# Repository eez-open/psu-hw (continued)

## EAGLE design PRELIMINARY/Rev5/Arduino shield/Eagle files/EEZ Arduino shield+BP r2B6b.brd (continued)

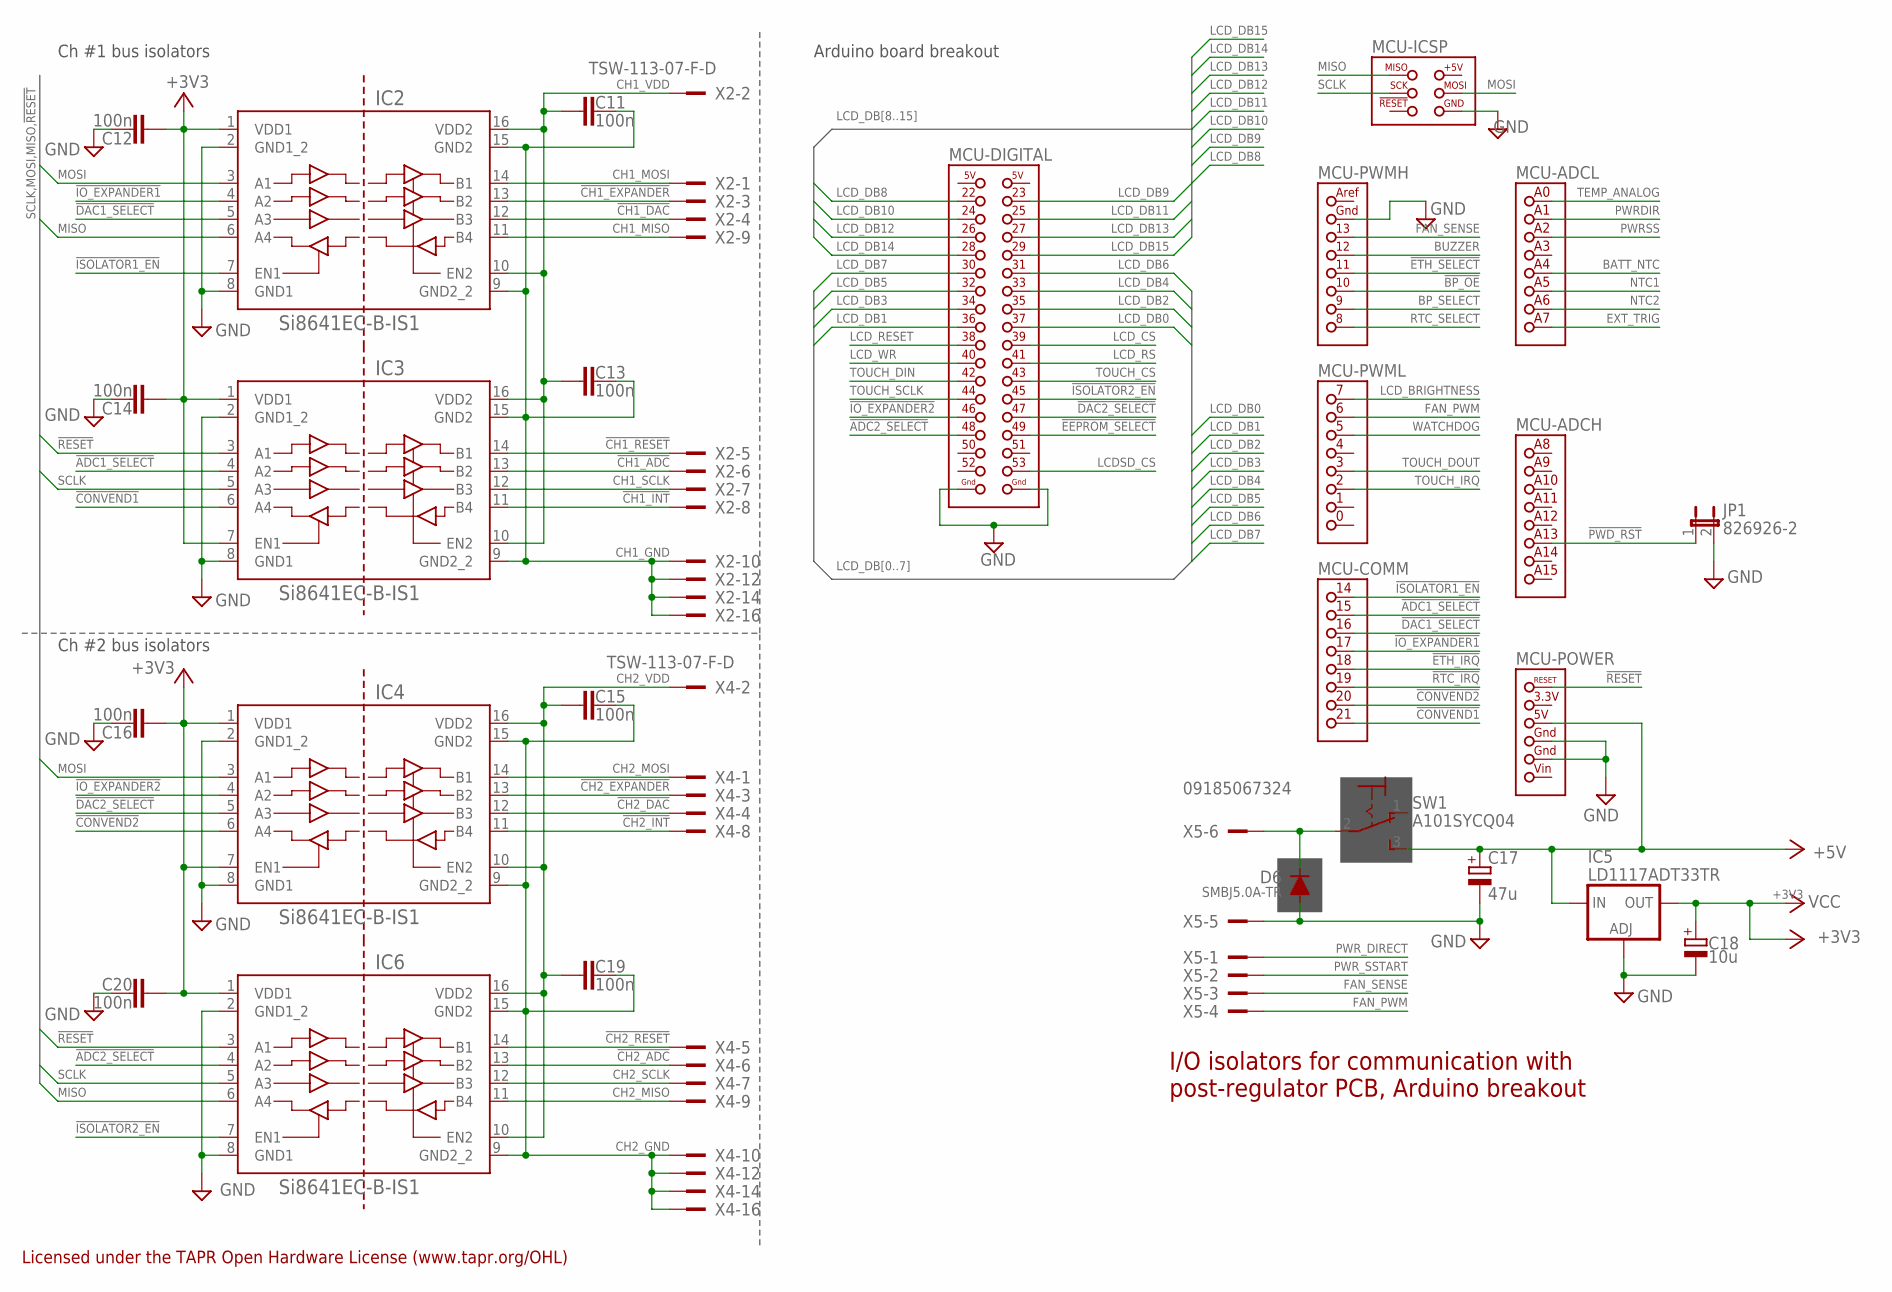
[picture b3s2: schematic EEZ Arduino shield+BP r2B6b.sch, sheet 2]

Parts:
C11, C12, C13, C14, C15, C16, C19, C20: 100n; C0603
C17: 47u; PANASONIC_C
C18: 10u; PANASONIC_C
D6: SMBJ5.0A-TR; DO214AA
IC2, IC3, IC4, IC6: Si8641EC-B-IS1; SOIC-16
IC5: LD1117ADT33TR; DPACK
JP1: 826926-2; JP1
MCU: Arduino Due; ARDUINO+ICSP_MIRROR
SW1: A101SYCQ04; M9040P
X2, X4: TSW-113-07-F-D; FARNELL 2025182
X5: 09185067324; IDC-6PIN

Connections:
!ADC1_SELECT: IC3.4 (A2), MCU.15
!ADC2_SELECT: IC6.4 (A2), MCU.48 (48(PL3))
!BP_OE: MCU.10; also elsewhere on the board
!CH1_ADC: IC3.13 (B2), X2.6
!CH1_DAC: IC2.12 (B3), X2.4
!CH1_EXPANDER: IC2.13 (B2), X2.3
!CH1_INT: IC3.11 (B4), X2.8
!CH1_RESET: IC3.14 (B1), X2.5
!CH2_ADC: IC6.13 (B2), X4.6
!CH2_DAC: IC4.12 (B3), X4.4
!CH2_EXPANDER: IC4.13 (B2), X4.3
!CH2_INT: IC4.11 (B4), X4.8
!CH2_RESET: IC6.14 (B1), X4.5
!CONVEND1: IC3.6 (A4), MCU.21
!CONVEND2: IC4.6 (A4), MCU.20
!DAC1_SELECT: IC2.5 (A3), MCU.16
!DAC2_SELECT: IC4.5 (A3), MCU.47 (47(PL4))
!EEPROM_SELECT: MCU.49 (49(PL2)); also elsewhere on the board
!ETH_IRQ: MCU.18; also elsewhere on the board
!ETH_SELECT: MCU.11; also elsewhere on the board
!IO_EXPANDER1: IC2.4 (A2), MCU.17
!IO_EXPANDER2: IC4.4 (A2), MCU.46 (46(PL5))
!ISOLATOR1_EN: IC2.7 (EN1), MCU.14
!ISOLATOR2_EN: IC6.7 (EN1), MCU.45 (45(PL6))
!PWD_RST: JP1.1, MCU.A13 (ADC13)
!RESET: IC3.3 (A1), IC6.3 (A1), MCU.RESET (!RESET); also elsewhere on the board
!RTC_IRQ: MCU.19; also elsewhere on the board
+3V3: C12.1, C14.1, C16.1, C18.1 (+), C20.1, IC2.1 (VDD1), IC3.1 (VDD1), IC3.7 (EN1), IC4.1 (VDD1), IC4.7 (EN1), IC5.4 (OUT), IC6.1 (VDD1); also elsewhere on the board
+5V: C17.1 (+), IC5.3 (IN), MCU.5V, SW1.3 (S); also elsewhere on the board
BATT_NTC: MCU.A4 (ADC4); also elsewhere on the board
BP_SELECT: MCU.9 (9(PH6)); also elsewhere on the board
BUZZER: MCU.12; also elsewhere on the board
CH1_GND: C11.2, C13.2, IC2.9 (GND2_2), IC2.15 (GND2), IC3.9 (GND2_2), IC3.15 (GND2), X2.10, X2.12, X2.14, X2.16; also elsewhere on the board
CH1_MISO: IC2.11 (B4), X2.9
CH1_MOSI: IC2.14 (B1), X2.1
CH1_SCLK: IC3.12 (B3), X2.7
CH1_VDD: C11.1, C13.1, IC2.10 (EN2), IC2.16 (VDD2), IC3.10 (EN2), IC3.16 (VDD2), X2.2; also elsewhere on the board
CH2_GND: C15.2, C19.2, IC4.9 (GND2_2), IC4.15 (GND2), IC6.9 (GND2_2), IC6.15 (GND2), X4.10, X4.12, X4.14, X4.16; also elsewhere on the board
CH2_MISO: IC6.11 (B4), X4.9
CH2_MOSI: IC4.14 (B1), X4.1
CH2_SCLK: IC6.12 (B3), X4.7
CH2_VDD: C15.1, C19.1, IC4.10 (EN2), IC4.16 (VDD2), IC6.10 (EN2), IC6.16 (VDD2), X4.2
EXT_TRIG: MCU.A7 (ADC7); also elsewhere on the board
FAN_PWM: MCU.6 (6(PH3)), X5.4
FAN_SENSE: MCU.13, X5.3
GND: C12.2, C14.2, C16.2, C17.2 (-), C18.2 (-), C20.2, D6.A, IC2.2 (GND1_2), IC2.8 (GND1), IC3.2 (GND1_2), IC3.8 (GND1), IC4.2 (GND1_2), IC4.8 (GND1), IC5.1 (ADJ), IC6.2 (GND1_2), IC6.8 (GND1), JP1.2, MCU.GND, MCU.GND1, MCU.GND2, MCU.GND3, MCU.GND4, MCU.ICSP_GND (GND), X5.5; also elsewhere on the board
LCDSD_CS: MCU.53 (53(PB2/MOSI)); also elsewhere on the board
LCD_BRIGHTNESS: MCU.7 (7(PH4)); also elsewhere on the board
LCD_CS: MCU.39 (39(PC0)); also elsewhere on the board
LCD_DB0: MCU.37 (37(PC2)); also elsewhere on the board
LCD_DB1: MCU.36 (36(PC3)); also elsewhere on the board
LCD_DB2: MCU.35 (35(PC4)); also elsewhere on the board
LCD_DB3: MCU.34 (34(PC5)); also elsewhere on the board
LCD_DB4: MCU.33 (33(PC6)); also elsewhere on the board
LCD_DB5: MCU.32 (32(PC7)); also elsewhere on the board
LCD_DB6: MCU.31 (31(PA7)); also elsewhere on the board
LCD_DB7: MCU.30 (30(PA6)); also elsewhere on the board
LCD_DB8: MCU.22; also elsewhere on the board
LCD_DB9: MCU.23; also elsewhere on the board
LCD_DB10: MCU.24 (24(PA0)); also elsewhere on the board
LCD_DB11: MCU.25 (25(PA1)); also elsewhere on the board
LCD_DB12: MCU.26 (26(PA2)); also elsewhere on the board
LCD_DB13: MCU.27 (27(PA3)); also elsewhere on the board
LCD_DB14: MCU.28 (28(PA4)); also elsewhere on the board
LCD_DB15: MCU.29 (29(PA5)); also elsewhere on the board
LCD_RESET: MCU.38 (38(PC1)); also elsewhere on the board
LCD_RS: MCU.41 (41(PG2)); also elsewhere on the board
LCD_WR: MCU.40 (40(PD7)); also elsewhere on the board
MISO: IC2.6 (A4), IC6.6 (A4), MCU.ICSP_MISO (MISO); also elsewhere on the board
MOSI: IC2.3 (A1), IC4.3 (A1), MCU.ICSP_MOSI (MOSI); also elsewhere on the board
unnamed: D6.C, SW1.2, X5.6
NTC1: MCU.A5 (ADC5); also elsewhere on the board
NTC2: MCU.A6 (ADC6); also elsewhere on the board
PWRDIR: MCU.A1 (ADC1); also elsewhere on the board
PWRSS: MCU.A2 (ADC2); also elsewhere on the board
PWR_DIRECT: X5.1; also elsewhere on the board
PWR_SSTART: X5.2; also elsewhere on the board
RTC_SELECT: MCU.8 (8(PH5)); also elsewhere on the board
SCLK: IC3.5 (A3), IC6.5 (A3), MCU.ICSP_SCK (SCK); also elsewhere on the board
TEMP_ANALOG: MCU.A0 (ADC0); also elsewhere on the board
TOUCH_CS: MCU.43 (43(PG0)); also elsewhere on the board
TOUCH_DIN: MCU.42 (42(PG1)); also elsewhere on the board
TOUCH_DOUT: MCU.3 (3(PE5)); also elsewhere on the board
TOUCH_IRQ: MCU.2 (2(PE4)); also elsewhere on the board
TOUCH_SCLK: MCU.44 (44(PL7)); also elsewhere on the board
WATCHDOG: MCU.5 (5(PE3)); also elsewhere on the board

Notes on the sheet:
I/O isolators for communication with
post-regulator PCB, Arduino breakout
Ch #1 bus isolators
Ch #2 bus isolators
Arduino board breakout
Licensed under the TAPR Open Hardware License (www.tapr.org/OHL)

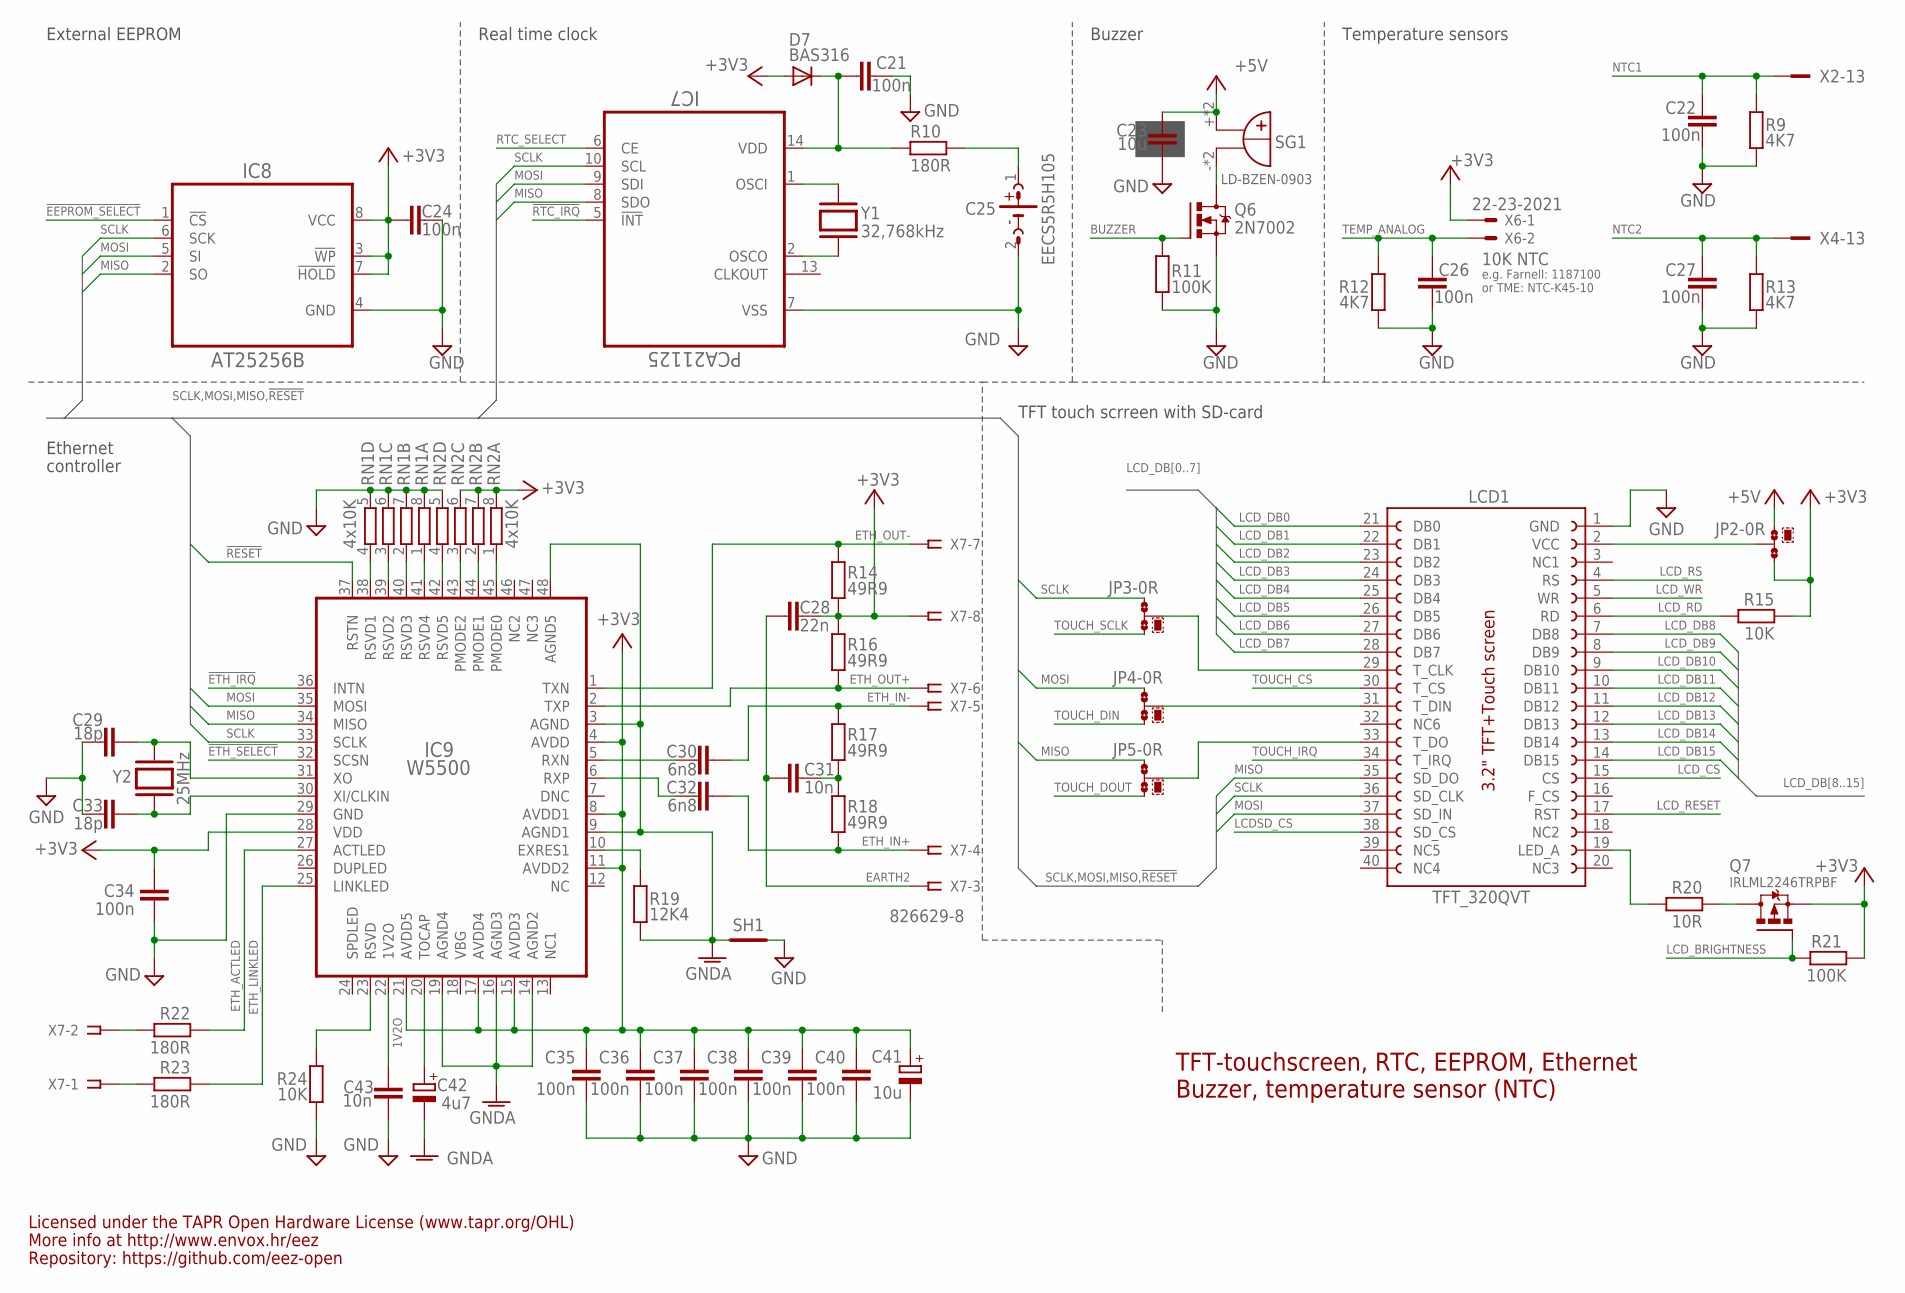
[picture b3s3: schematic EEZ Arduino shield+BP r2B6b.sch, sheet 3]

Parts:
C21, C22, C24, C26, C27, C34, C35, C36, C37, C38, C39, C40: 100n; C0603
C23: 10u; C1206
C25: EECS5R5H105; SG-R20MM
C28: 22n; C0805
C29, C33: 18p; C0603
C30, C32: 6n8; C0603
C31, C43: 10n; C0805
C41: 10u; EC1206
C42: 4u7; EC1206
D7: BAS316; SOD323-W
IC7: PCA21125; SOP65P640X120-14N
IC8: AT25256B; SOIC127P600X175-8N
IC9: W5500; TQFP48-7X7
JP2, JP3, JP4, JP5: 0R-JUMPA; A0R-JMP
LCD1: TFT_320QVT; LCD_TFT_320QVT_MIRROR
Q6: 2N7002; SOT103P240X110-3N
Q7: IRLML2246TRPBF; SOT95P237X112-3N
R9, R12, R13: 4K7; R0805
R10, R22, R23: 180R; R0805
R11, R21: 100K; R0805
R14, R16, R17, R18: 49R9; R0805
R15, R24: 10K; R0805
R19: 12K4; R0805
R20: 10R; R0805
RN1, RN2: 4x10K; CAY16
SG1: LD-BZEN-0903; BUZZER
SH1: SHORTNOHOLE; SHORT_NOHOLE
X2, X4: TSW-113-07-F-D; FARNELL 2025182
X6: 22-23-2021; MPN 22-23-2021
X7: 826629-8; SSW-108-02-S-S; MPN SSW-108-02-S-S
Y1: 32,768kHz; R26_XTAL
Y2: 25MHz; HC-49/4H

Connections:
1V2O: C43.2, IC9.22 (1V2O)
!EEPROM_SELECT: IC8.1 (!CS); also elsewhere on the board
!ETH_IRQ: IC9.36 (INTN); also elsewhere on the board
!ETH_SELECT: IC9.32 (SCSN); also elsewhere on the board
!RESET: IC9.37 (RSTN); also elsewhere on the board
!RTC_IRQ: IC7.5 (!INT); also elsewhere on the board
+3V3: C24.1, C28.1, C34.2, C35.1, C36.1, C37.1, C38.1, C39.1, C40.1, C41.+, D7.A, IC8.3 (!WP), IC8.7 (!HOLD), IC8.8 (VCC), IC9.4 (AVDD), IC9.8 (AVDD1), IC9.11 (AVDD2), IC9.15 (AVDD3), IC9.17 (AVDD4), IC9.21 (AVDD5), IC9.28 (VDD), JP2.3, Q7.2 (S), R14.1, R15.2, R16.2, R21.2, RN2.6 (2), RN2.7 (2), RN2.8 (2), X6.1, X7.8; also elsewhere on the board
+5V: C23.2, JP2.1, SG1.+, SG1.+B (+); also elsewhere on the board
BUZZER: Q6.1 (G), R11.2; also elsewhere on the board
EARTH2: C28.2, C31.2, X7.3; also elsewhere on the board
ETH_ACTLED: IC9.27 (ACTLED), R22.1
ETH_IN+: C32.1, R18.1, X7.4
ETH_IN-: C30.1, R17.2, X7.5
ETH_LINKLED: IC9.25 (LINKLED), R23.1
ETH_OUT+: IC9.2 (TXP), R16.1, X7.6
ETH_OUT-: IC9.1 (TXN), R14.2, X7.7
GND: C21.1, C22.1, C23.1, C24.2, C25.2 (-), C26.1, C27.1, C29.2, C33.2, C34.1, C35.2, C36.2, C37.2, C38.2, C39.2, C40.2, C41.-, C43.1, IC7.7 (VSS), IC8.4 (GND), IC9.29 (GND), LCD1.1 (GND), Q6.2 (S), R9.2, R11.1, R12.2, R13.2, R24.1, RN1.5 (2), RN1.6 (2), RN1.7 (2), RN1.8 (2), RN2.5 (2), SH1.P$1 (GND_A); also elsewhere on the board
GNDA: C42.-, IC9.3 (AGND), IC9.9 (AGND1), IC9.14 (AGND2), IC9.16 (AGND3), IC9.19 (AGND4), IC9.48 (AGND5), R19.1, SH1.P$2 (GND_B)
LCDSD_CS: LCD1.38 (SD_CS); also elsewhere on the board
LCD_BRIGHTNESS: Q7.1 (G), R21.1; also elsewhere on the board
LCD_CS: LCD1.15 (CS); also elsewhere on the board
LCD_DB0: LCD1.21 (DB0); also elsewhere on the board
LCD_DB1: LCD1.22 (DB1); also elsewhere on the board
LCD_DB2: LCD1.23 (DB2); also elsewhere on the board
LCD_DB3: LCD1.24 (DB3); also elsewhere on the board
LCD_DB4: LCD1.25 (DB4); also elsewhere on the board
LCD_DB5: LCD1.26 (DB5); also elsewhere on the board
LCD_DB6: LCD1.27 (DB6); also elsewhere on the board
LCD_DB7: LCD1.28 (DB7); also elsewhere on the board
LCD_DB8: LCD1.7 (DB8); also elsewhere on the board
LCD_DB9: LCD1.8 (DB9); also elsewhere on the board
LCD_DB10: LCD1.9 (DB10); also elsewhere on the board
LCD_DB11: LCD1.10 (DB11); also elsewhere on the board
LCD_DB12: LCD1.11 (DB12); also elsewhere on the board
LCD_DB13: LCD1.12 (DB13); also elsewhere on the board
LCD_DB14: LCD1.13 (DB14); also elsewhere on the board
LCD_DB15: LCD1.14 (DB15); also elsewhere on the board
LCD_RD: LCD1.6 (RD), R15.1
LCD_RESET: LCD1.17 (RST); also elsewhere on the board
LCD_RS: LCD1.4 (RS); also elsewhere on the board
LCD_WR: LCD1.5 (WR); also elsewhere on the board
LED_A: LCD1.19 (LED_A), R20.2
MISO: IC7.8 (SDO), IC8.2 (SO), IC9.34 (MISO), JP5.1, LCD1.35 (SD_DO); also elsewhere on the board
MOSI: IC7.9 (SDI), IC8.5 (SI), IC9.35 (MOSI), JP4.1, LCD1.37 (SD_IN); also elsewhere on the board
unnamed: JP5.2, LCD1.33 (T_DO)
unnamed: C33.1, IC9.30 (XI/CLKIN), Y2.2
unnamed: IC9.23 (RSVD), R24.2
unnamed: C30.2, IC9.5 (RXN)
unnamed: C32.2, IC9.6 (RXP)
unnamed: JP2.2, LCD1.2 (VCC)
unnamed: IC9.43 (PMODE2), RN2.3 (1)
unnamed: IC9.44 (PMODE1), RN2.2 (1)
unnamed: Q7.3 (D), R20.1
unnamed: IC9.45 (PMODE0), RN2.1
unnamed: IC9.42 (RSVD5), RN2.4 (1)
unnamed: JP4.2, LCD1.31 (T_DIN)
unnamed: JP3.2, LCD1.29 (T_CLK)
unnamed: C25.1 (+), R10.1
unnamed: IC9.38 (RSVD1), RN1.4 (1)
unnamed: IC7.1 (OSCI), Y1.1
unnamed: IC7.2 (OSCO), Y1.2
unnamed: IC9.39 (RSVD2), RN1.3 (1)
unnamed: IC9.41 (RSVD4), RN1.1
unnamed: IC9.40 (RSVD3), RN1.2 (1)
unnamed: R23.2, X7.1
unnamed: R22.2, X7.2
unnamed: IC9.10 (EXRES1), R19.2
unnamed: Q6.3 (D), SG1.-, SG1.-B (-)
unnamed: C29.1, IC9.31 (XO), Y2.1
unnamed: C21.2, D7.C, IC7.14 (VDD), R10.2
unnamed: C31.1, R17.1, R18.2
NTC1: C22.2, R9.1, X2.13; also elsewhere on the board
NTC2: C27.2, R13.1, X4.13; also elsewhere on the board
RTC_SELECT: IC7.6 (CE); also elsewhere on the board
SCLK: IC7.10 (SCL), IC8.6 (SCK), IC9.33 (SCLK), JP3.1, LCD1.36 (SD_CLK); also elsewhere on the board
TEMP_ANALOG: C26.2, R12.1, X6.2; also elsewhere on the board
TOCAP: C42.+, IC9.20 (TOCAP)
TOUCH_CS: LCD1.30 (T_CS); also elsewhere on the board
TOUCH_DIN: JP4.3; also elsewhere on the board
TOUCH_DOUT: JP5.3; also elsewhere on the board
TOUCH_IRQ: LCD1.34 (T_IRQ); also elsewhere on the board
TOUCH_SCLK: JP3.3; also elsewhere on the board

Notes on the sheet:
TFT-touchscreen, RTC, EEPROM, Ethernet
e.g. Farnell: 1187100
10K NTC
or TME: NTC-K45-10
Buzzer, temperature sensor (NTC)
External EEPROM
Real time clock
Buzzer
Temperature sensors
TFT touch scrreen with SD-card
Ethernet
controller
Licensed under the TAPR Open Hardware License (www.tapr.org/OHL)
Repository: https://github.com/eez-open
More info at http://www.envox.hr/eez

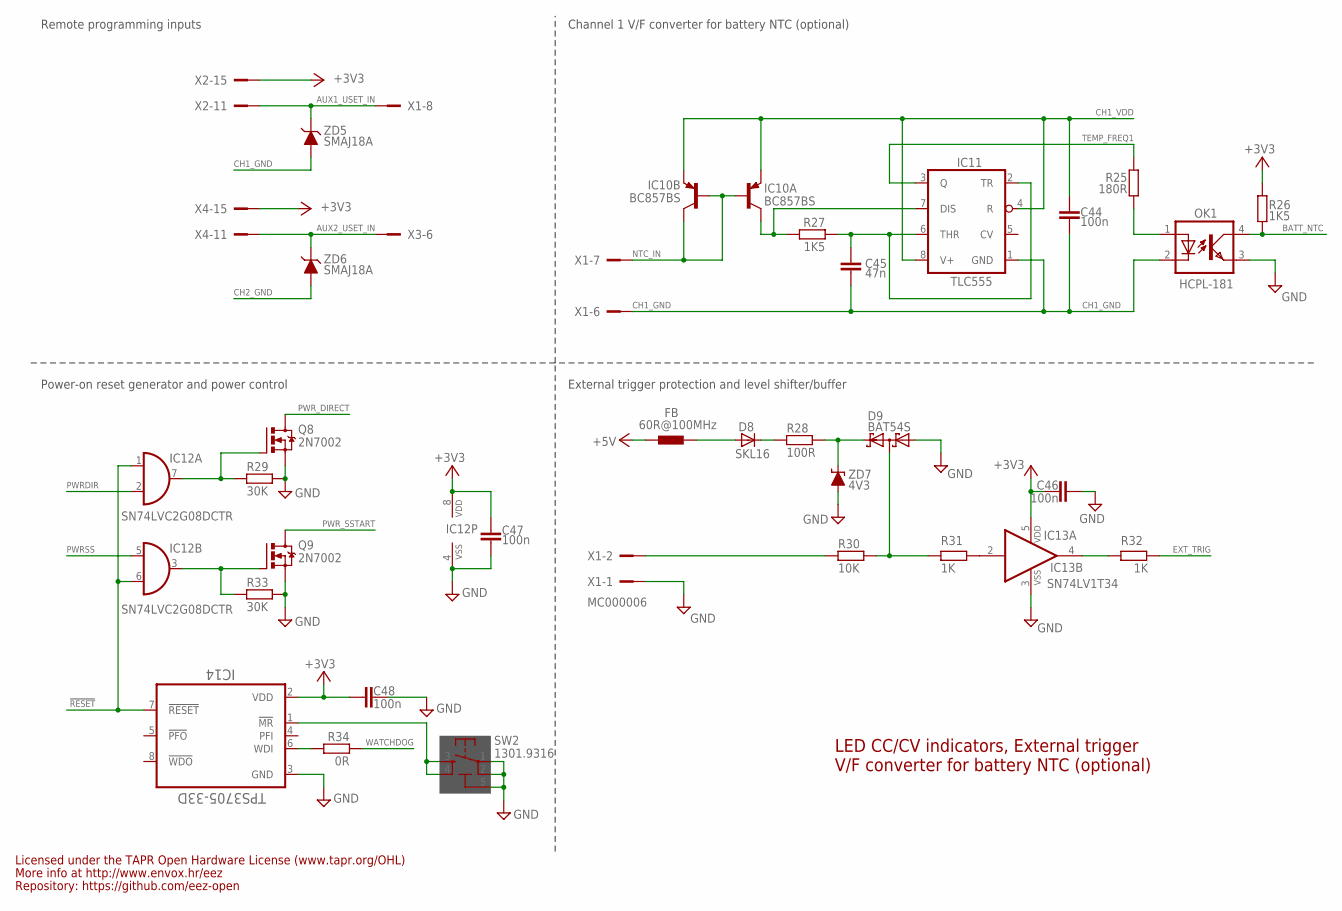
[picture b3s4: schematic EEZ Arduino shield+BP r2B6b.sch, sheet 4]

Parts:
C44, C46, C47, C48: 100n; C0603
C45: 47n; C0805
D8: SKL16; DO214AC
D9: BAT54S; SOT23
FB: 60R@100MHz; BEAD0603
IC10: BC857BS; SOT65P210X110-6N
IC11: TLC555; SOIC127P600X175-8N
IC12: SN74LVC2G08DCTR; SOP65P400X130-8N
IC13: SN74LV1T34; SOT95P280X145-5N
IC14: TPS3705-33D; SOIC127P600X175-8N
OK1: HCPL-181
Q8, Q9: 2N7002; SOT103P240X110-3N
R25: 180R; R0805
R26, R27: 1K5; R0805
R28: 100R; R0805
R29, R33: 30K; R0805
R30: 10K; R1206
R31, R32: 1K; R0805
R34: 0R; R0805
SW2: 1301.9316; TACTM-6XN
X1: MC000006; MC000006_MIRROR; FARNELL 2007972
X2, X4: TSW-113-07-F-D; FARNELL 2025182
X3: MC000005; MC000005_MIRROR
ZD5, ZD6: SMAJ18A; DO214AC
ZD7: 4V3; MINIMELF

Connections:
!RESET: IC12.1 (I0), IC12.6 (I1), IC14.7 (!RESET); also elsewhere on the board
+3V3: C46.1, C47.2, C48.2, IC12.8 (VDD), IC13.5 (VDD), IC14.2 (VDD), R26.1, X2.15, X4.15; also elsewhere on the board
+5V: FB.P$1 (1); also elsewhere on the board
AUX1_USET_IN: X1.8, X1.8.1, X2.11, ZD5.C
AUX2_USET_IN: X3.6, X3.6.1, X4.11, ZD6.C
BATT_NTC: OK1.4 (COL), R26.2; also elsewhere on the board
CH1_GND: C44.2, C45.1, IC11.1 (GND), OK1.2 (C), X1.6, X1.6.1, ZD5.A; also elsewhere on the board
CH1_VDD: C44.1, IC10.1 (E), IC10.4 (E), IC11.4 (R), IC11.8 (V+); also elsewhere on the board
CH2_GND: ZD6.A; also elsewhere on the board
EXT_TRIG: R32.1; also elsewhere on the board
GND: C46.2, C47.1, C48.1, D9.1 (A1), IC12.4 (VSS), IC13.3 (VSS), IC14.3 (GND), OK1.3 (EMIT), Q8.2 (S), Q9.2 (S), R29.2, R33.2, SW2.1, SW2.2, SW2.5 (5-GND), X1.1, X1.1.1, ZD7.A; also elsewhere on the board
unnamed: OK1.1 (A), R25.2
unnamed: IC10.6 (C), IC11.7 (DIS), R27.1
unnamed: C45.2, IC11.2 (TR), IC11.6 (THR), R27.2
unnamed: D9.2 (C2), R28.1, ZD7.C
unnamed: D9.3 (C1A2), R30.2, R31.2
unnamed: IC13.2 (I), R31.1
unnamed: IC13.4 (O), R32.2
unnamed: D8.C, R28.2
unnamed: R30.1, X1.2, X1.2.1
unnamed: D8.A, FB.P$2 (2)
unnamed: IC14.1 (!MR), SW2.3, SW2.4
unnamed: IC14.6 (WDI), R34.1
unnamed: IC12.7 (O), Q8.1 (G), R29.1
unnamed: IC12.3 (O), Q9.1 (G), R33.1
NTC_IN: IC10.2 (B), IC10.3 (C), IC10.5 (B), X1.7, X1.7.1
PWRDIR: IC12.2 (I1); also elsewhere on the board
PWRSS: IC12.5 (I0); also elsewhere on the board
PWR_DIRECT: Q8.3 (D); also elsewhere on the board
PWR_SSTART: Q9.3 (D); also elsewhere on the board
TEMP_FREQ1: IC11.3 (Q), R25.1
WATCHDOG: R34.2; also elsewhere on the board

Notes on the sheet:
V/F converter for battery NTC (optional)
LED CC/CV indicators, External trigger
Channel 1 V/F converter for battery NTC (optional)
External trigger protection and level shifter/buffer
Remote programming inputs
Licensed under the TAPR Open Hardware License (www.tapr.org/OHL)
Repository: https://github.com/eez-open
More info at http://www.envox.hr/eez
Power-on reset generator and power control

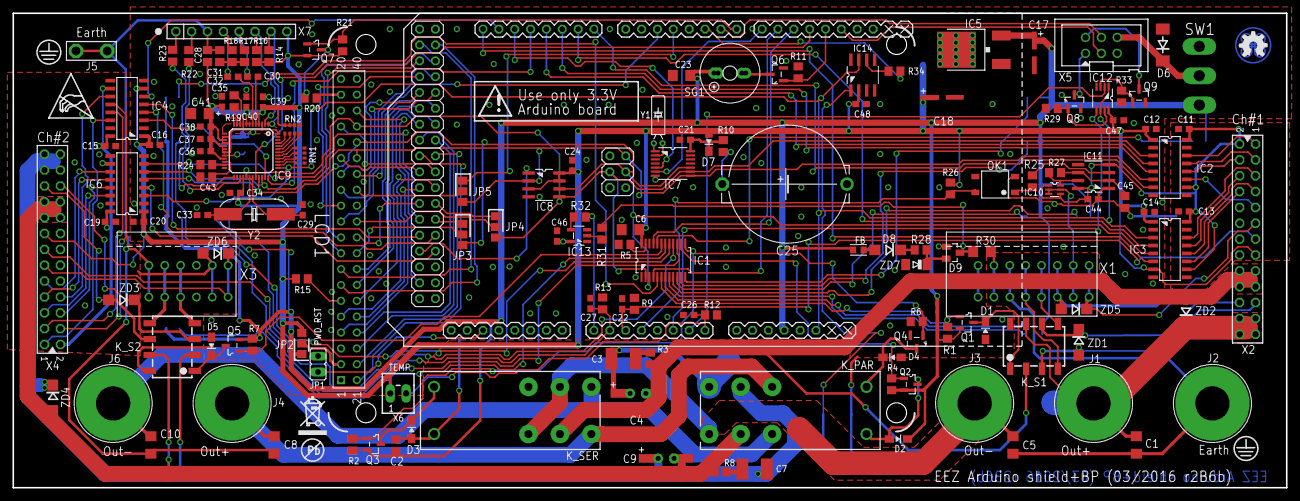
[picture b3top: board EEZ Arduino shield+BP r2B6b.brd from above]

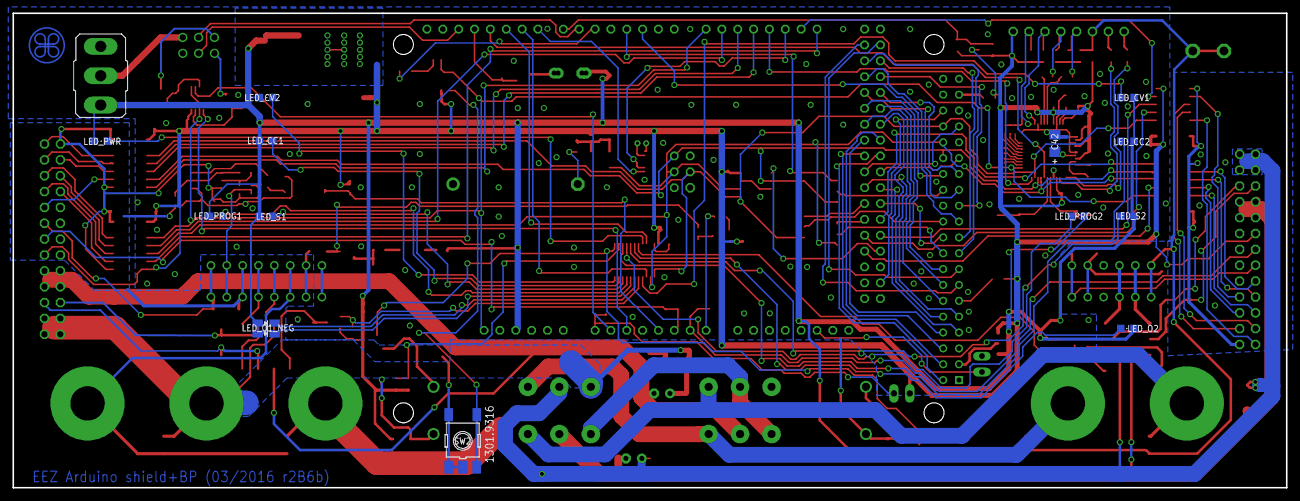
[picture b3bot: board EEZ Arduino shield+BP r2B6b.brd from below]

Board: 3 copper layers, 204.0 x 76.0 mm, 170 parts (14 on the bottom side), 183 nets.

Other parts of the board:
EEZ_SIGNATURE: SIGNATURESMALL; SIGNATURE_5MM
U$2: RECYCLE_BIN1/8
U$3: PB_SMALL
U$4: ESD_SYMBOL

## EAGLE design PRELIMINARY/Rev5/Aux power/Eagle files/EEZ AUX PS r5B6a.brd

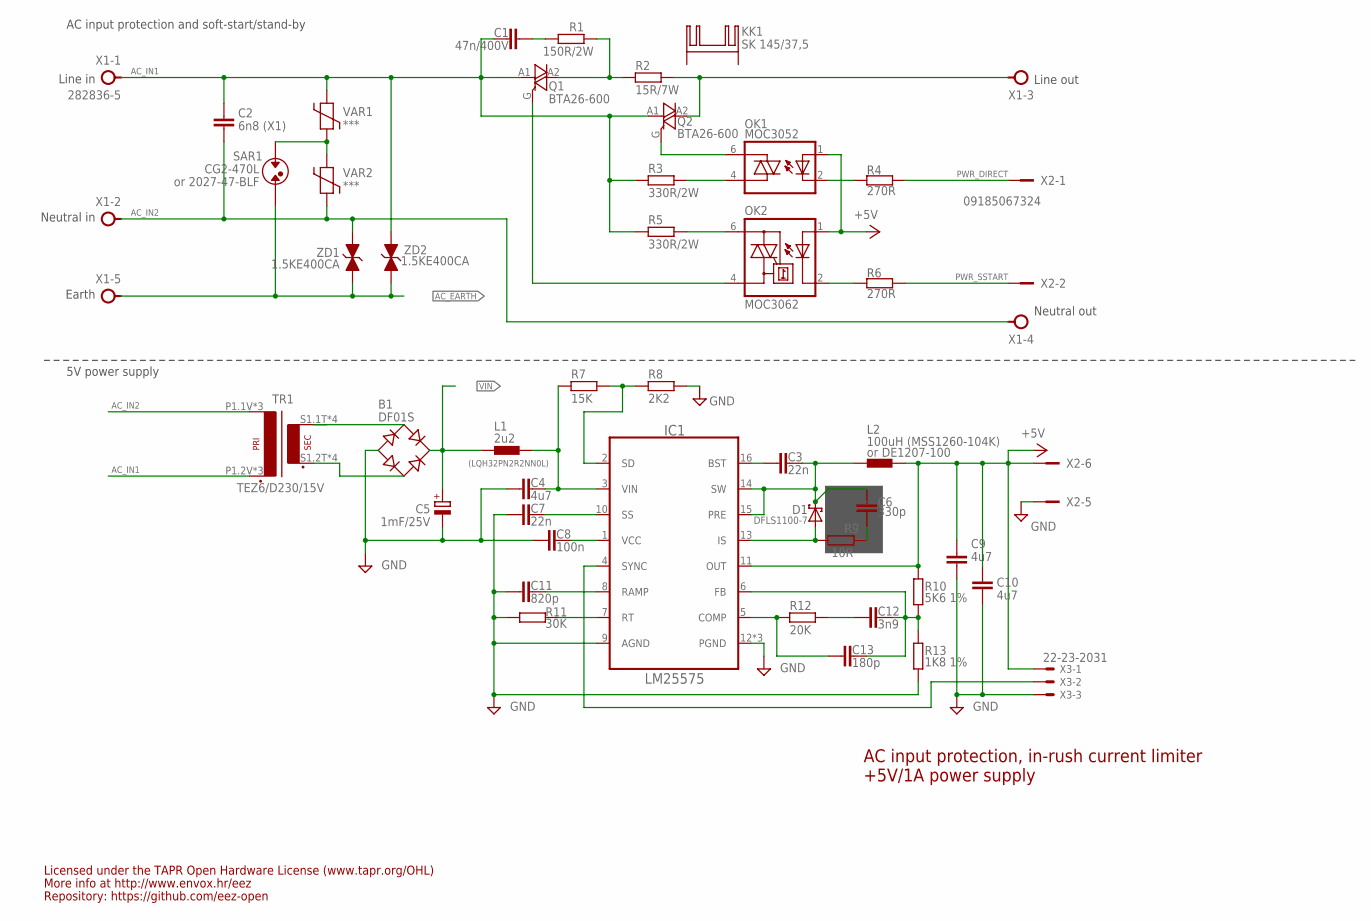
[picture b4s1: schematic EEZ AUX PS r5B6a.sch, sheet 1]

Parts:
B1: DF01S; DFS
C1: 47n/400V; C075-052X106
C2: 6n8 (X1); C102-064X133
C3, C7: 22n; C0805
C4, C9, C10: 4u7; C1210
C5: 1mF/25V; ECAP5/10.5
C6: 330p; C0805
C8: 100n; C0805
C11: 820p; C0805
C12: 3n9; C0805
C13: 180p; C0805
D1: DFLS1100-7; SOD123
IC1: LM25575; SOP65P640X110-17N_HOLE
KK1: SK 145/37,5; SK145
L1: 2u2; L1210
L2: 100uH (MSS1260-104K); MSS1278
OK1: MOC3052; DIL6-SMD
OK2: MOC3062; DIL6-SMD; MPN MOC3033S-M
Q1, Q2: BTA26-600; TOP3S-1
R1: 150R/2W; R2512
R2: 15R/7W; R_0913
R3, R5: 330R/2W; R2512
R4, R6: 270R; R0805
R7: 15K; R0805
R8: 2K2; R0805
R9: 10R; R1206
R10: 5K6 1%; R0805
R11: 30K; R0805
R12: 20K; R0805
R13: 1K8 1%; R0805
SAR1: CG2-470L; SAR
TR1: TEZ6/D230/15V; PCB_TRAFO6VA_TEZ+VPP
VAR1, VAR2: ***; VARISTOR
X1: 282836-5; TBLOCK5.0_5
X2: 09185067324; IDC-6PIN
X3: 22-23-2031
ZD1, ZD2: 1.5KE400CA; DO201-BIDIR

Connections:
+5V: C9.1, C10.1, IC1.11 (OUT), L2.2, OK1.1 (A), OK2.1 (A), R10.1, X2.6, X3.1; also elsewhere on the board
AC_EARTH: SAR1.P$2, X1.5, ZD1.C (1), ZD2.C (1); also elsewhere on the board
AC_IN1: C1.2, C2.1, Q1.A1, Q2.A1, R3.2, R5.2, TR1.P1.2V (P2), TR1.P2.2V (P2), TR1.P2_TEZ (P2), VAR1.P$2, X1.1, ZD2.A (2)
AC_IN2: C2.2, TR1.P1.1V (P1), TR1.P1_TEZ (P1), TR1.P2.1V (P1), VAR2.P$1, X1.2, X1.4, ZD1.A (2)
DC_PREG1: C4.1, IC1.3 (VIN), L1.2, R7.2
GND: B1.-, C4.2, C5.-, C7.2, C8.1, C9.2, C10.2, C11.1, IC1.9 (AGND), IC1.12 (PGND), IC1.TP (PGND), IC1.TP2 (PGND), R8.1, R11.2, R13.2, X2.5, X3.3; also elsewhere on the board
IS: D1.A, IC1.13 (IS), R9.1
unnamed: C6.2, R9.2
unnamed: OK1.6 (A2), Q2.G
unnamed: OK1.4 (A1), R3.1
unnamed: OK2.4 (A1), Q1.G
unnamed: OK1.2 (C), R4.1
unnamed: OK2.2 (C), R6.1
unnamed: OK2.6 (A2), R5.1
unnamed: Q2.A2, R2.2, X1.3
unnamed: B1.AC1, TR1.S1.1T (S1), TR1.S1.1V (S1), TR1.S2.1T (S1), TR1.S2.1V (S1)
unnamed: IC1.4 (SYNC), X3.2
unnamed: C1.1, R1.1
unnamed: B1.AC2, TR1.S1.2T (S2), TR1.S1.2V (S2), TR1.S2.2T (S2), TR1.S2.2V (S2)
unnamed: Q1.A2, R1.2, R2.1
unnamed: C12.2, R12.2
unnamed: SAR1.P$1, VAR1.P$1, VAR2.P$2
unnamed: C12.1, C13.1, IC1.6 (FB), R10.2, R13.1
unnamed: C3.2, IC1.16 (BST)
unnamed: C13.2, IC1.5 (COMP), R12.1
unnamed: IC1.7 (RT), R11.1
unnamed: C8.2, IC1.1 (VCC)
unnamed: C11.2, IC1.8 (RAMP)
unnamed: C7.1, IC1.10 (SS)
unnamed: IC1.2 (SD), R7.1, R8.2
PWR_DIRECT: R4.2, X2.1
PWR_SSTART: R6.2, X2.2
SW: C3.1, C6.1, D1.C, IC1.14 (SW), IC1.15 (PRE), L2.1
VIN: B1.+, C5.+, L1.1; also elsewhere on the board

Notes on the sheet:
AC input protection, in-rush current limiter
+5V/1A power supply
Line in
Neutral in
Earth
or DE1207-100
Line out
Neutral out
or 2027-47-BLF
(LQH32PN2R2NN0L)
Licensed under the TAPR Open Hardware License (www.tapr.org/OHL)
Repository: https://github.com/eez-open
More info at http://www.envox.hr/eez
5V power supply
AC input protection and soft-start/stand-by

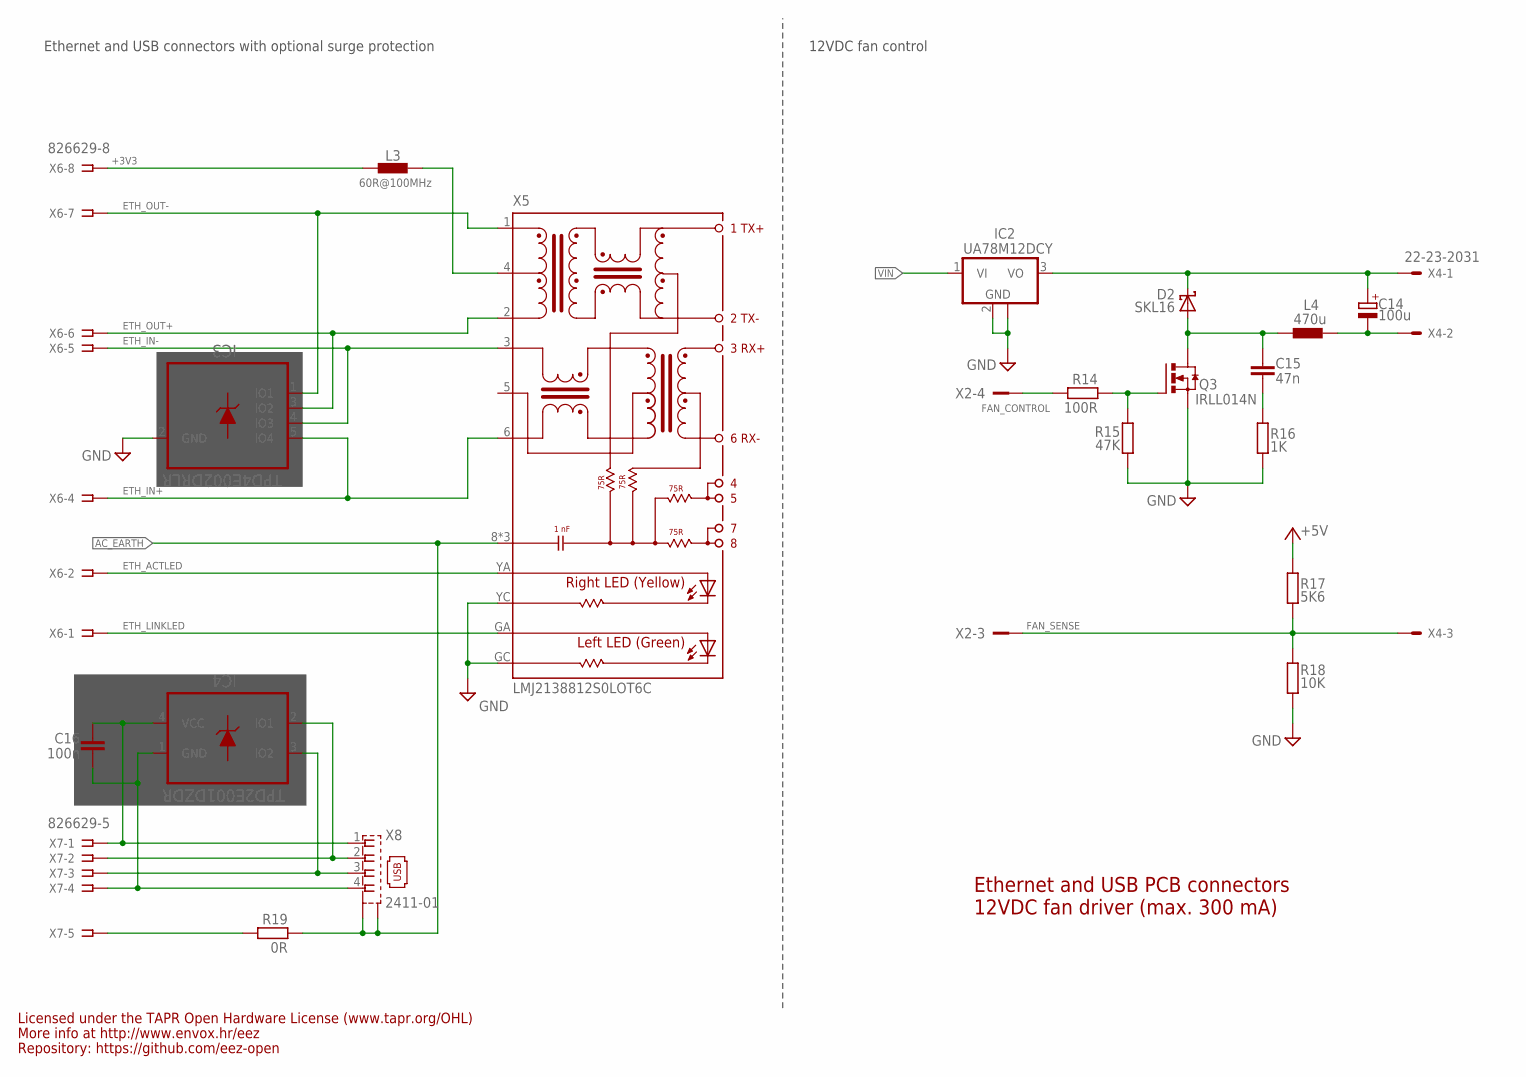
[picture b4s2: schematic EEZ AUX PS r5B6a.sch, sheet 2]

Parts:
C14: 100u; CAPAE660X610N
C15: 47n; C0805
C16: 100n; C0805
D2: SKL16; SOD123
IC2: UA78M12DCY; SOT230P700X180-4N
IC3: TPD4E002DRLR; SOT50P280X60-5N
IC4: TPD2E001DZDR; SOP192P292X122-4N
L3: 60R@100MHz; BEAD0603
L4: 470u; DE0704
Q3: IRLL014N; SOT223
R14: 100R; R0805
R15: 47K; R0805
R16: 1K; R0805
R17: 5K6; R0805
R18: 10K; R0805
R19: 0R; R0805
X2: 09185067324; IDC-6PIN
X4: 22-23-2031
X5: LMJ2138812S0LOT6C; RJ45-VERT
X6: 826629-8; SSW-108-02-S-S
X7: 826629-5; SSW-105-02-S-S
X8: 2411-01; KUSBVX-BS1N

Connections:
+3V3: L3.P$2 (2), X6.8
+5V: R17.1; also elsewhere on the board
AC_EARTH: R19.1, X5.8 (SH), X5.SH1 (SH), X5.SH2 (SH), X8.M1 (S1), X8.M2 (S2); also elsewhere on the board
ETH_ACTLED: X5.YA (YELLOW_A), X6.2
ETH_IN+: IC3.5 (IO4), X5.6 (RD-), X6.4
ETH_IN-: IC3.4 (IO3), X5.3 (RD+), X6.5
ETH_LINKLED: X5.GA (GREEN-A), X6.1
ETH_OUT+: IC3.3 (IO2), X5.2 (TD-), X6.6
ETH_OUT-: IC3.1 (IO1), X5.1 (TD+), X6.7
FAN_CONTROL: R14.2, X2.4
FAN_OUT: C15.2, D2.A, L4.2, Q3.2 (D), Q3.4 (D)
FAN_SENSE: R17.2, R18.1, X2.3, X4.3
GND: IC2.2 (GND), IC2.4 (GND), IC3.2 (GND), Q3.3 (S), R15.1, R16.1, R18.2, X5.GC (GREEN-C), X5.YC (YELLOW-C); also elsewhere on the board
unnamed: C16.2, IC4.4 (VCC), X7.1, X8.1
unnamed: C15.1, R16.2
unnamed: R19.2, X7.5
unnamed: Q3.1 (G), R14.1, R15.2
unnamed: IC4.2 (IO1), X7.2, X8.2
unnamed: C14.1 (+), D2.C, IC2.3 (VO), X4.1
unnamed: C14.2 (-), L4.1, X4.2
unnamed: IC4.3 (IO2), X7.3, X8.3
unnamed: C16.1, IC4.1 (GND), X7.4, X8.4
unnamed: L3.P$1 (1), X5.4 (CT)
VIN: IC2.1 (VI); also elsewhere on the board

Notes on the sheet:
Ethernet and USB PCB connectors
12VDC fan driver (max. 300 mA)
Licensed under the TAPR Open Hardware License (www.tapr.org/OHL)
Repository: https://github.com/eez-open
More info at http://www.envox.hr/eez
Ethernet and USB connectors with optional surge protection
12VDC fan control
